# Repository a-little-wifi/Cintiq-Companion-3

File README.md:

# Cintiq Companion 3

I have a dead Cintiq 13HD (pen+touch) that won't display anything. I know the lcd works, tested it in my Cintiq Companion, so the board must be dead. I wanna make a new one, that you can build a computer into, or with USB-C maybe. 

Wacom made a tablet PC based on the 13HD called the Cintiq Companion, then they made a Cintiq Companion 2, so this will be the Cintiq Companion 3.

Contains a USB2514Bi 4-port USB hub connected as follows:

- Port 1: Pen digitizer?
- Port 2: External USB port
- Port 3: USB UART converter
- Port 4: Touch panel digitizer

I thought the USB UART chip (SILABS CP2102) was for the pen digitizer, but it appears to connect to the RTD2483AD display controller chip instead, might be for brightness control.

This is probably the right connector for the touch panel: https://www.lcsc.com/product-detail/Wire-To-Board-Connector_HCTL-HC-0-8-5PWT_C2845346.html  

Possible ipex connectors:  
https://www.lcsc.com/product-detail/Card-Edge-Connectors_JUSHUO-ALC04-S30EIA-00_C2842535.html  
https://www.lcsc.com/product-detail/FFC-FPC-Connectors_Lian-Xin-Technology-20455-030E-12_C7527730.html

The scanned images are 300ppi, for size reference

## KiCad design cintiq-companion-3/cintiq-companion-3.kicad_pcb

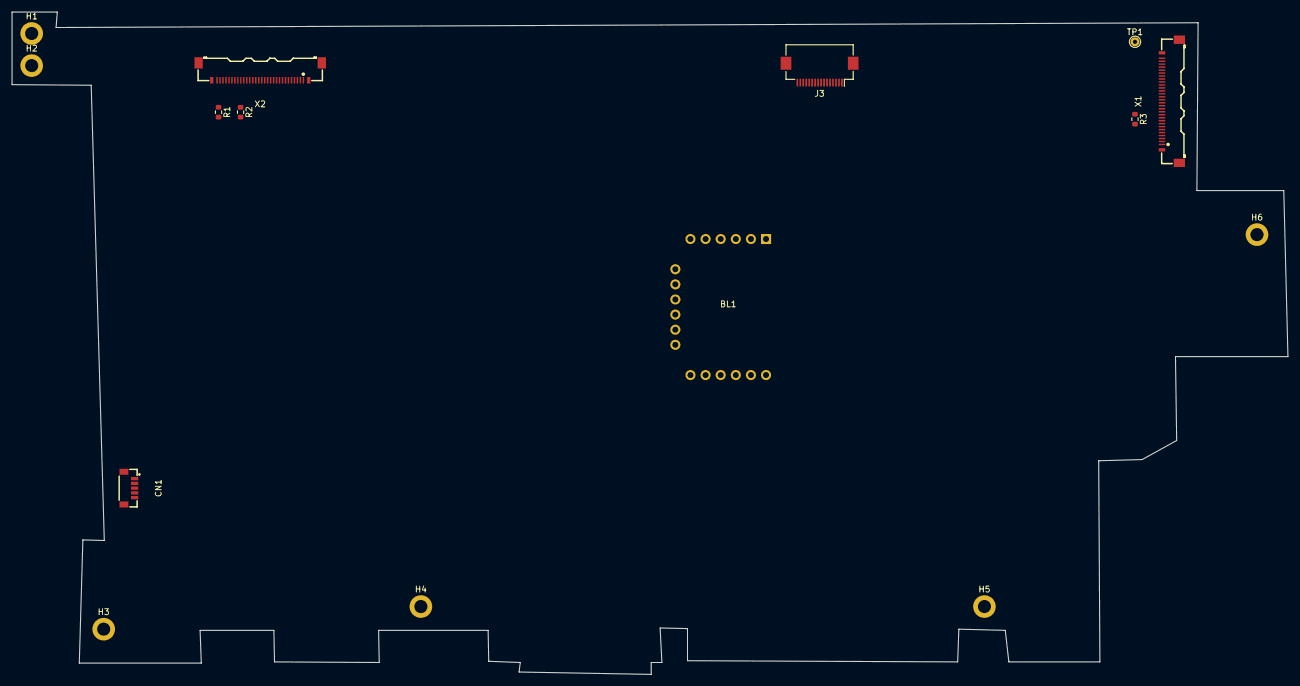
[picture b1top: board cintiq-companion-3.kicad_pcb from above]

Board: 2 copper layers, 214.4 x 111.3 mm, 15 parts (0 on the bottom side), 21 nets, no tracks yet.

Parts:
BL1: koyomi-backlight
CN1: 13HD_fingerpanel; minitek5p0.8mm
H1, H2, H3, H4, H5, H6: MountingHole_Pad; MountingHole_2.2mm_M2_DIN965_Pad
J3: 13HD_buttonboard; Hirose_FH12-16S-0.5SH_1x16-1MP_P0.50mm_Horizontal
R1, R2: 4.7kΩ; R_0603_1608Metric
R3: 47kΩ; R_0603_1608Metric
TP1: Something; TestPoint_THTPad_D1.5mm_Drill0.7mm
X1: 13HD_eDP; 30pipex
X2: 13HD_penpanel; 30pipex

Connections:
+3.3V: BL1.8 (+3.3V), J3.1, J3.2, X1.18, X1.19
+5V: BL1.4 (+5V), CN1.5, X2.10, X2.11
+VBL: BL1.1 (VAD), X1.4, X1.5
/BL_return_1: BL1.13 (LED1), X1.10
/BL_return_2: BL1.14 (LED2), X1.9
/BL_return_3: BL1.15 (LED3), X1.8
/BL_return_4: BL1.16 (LED4), X1.7
/RTD2483AD_pin_105: R1.1, X2.28
/RTD2483AD_pin_110: R2.1, X2.24
/bottombutton: J3.6, X2.19
/downbutton: J3.7, X2.15
/eDP_HPD: R3.1, X1.15
/leftbutton: J3.9, X2.16
/middlebottombutton: J3.5, X2.20
/middlebutton: J3.11, X2.14
/middletopbutton: J3.4, X2.21
/rightbutton: J3.10, X2.18
/topbutton: J3.3, X2.22
/upbutton: J3.8, X2.17
GND: BL1.3 (GND), BL1.7 (GND), CN1.1, CN1.6, CN1.7, H1.1, H2.1, H3.1, H4.1, H5.1, H6.1, J3.15, J3.16, J3.MP (MountPin), R1.2, R2.2, R3.2, X1.16, X1.20, X1.23, X1.26, X1.29, X1.31, X1.32, X1.33, X1.34, X2.5, X2.6, X2.12, X2.13, X2.23, X2.27, X2.31, X2.32, X2.33, X2.34
unnamed: TP1.1, X1.30

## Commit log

2024-05-09 Created KiCad project
2024-05-09 Added readme
2024-05-09 added generic connector symbols and connected ground pins
2024-05-09 Added marco pictures of connectors
2024-05-09 rotated images + ran some signals
2024-05-09 Added CP2102 usb uart bridge
2024-05-09 Added USB/UART notes to readme
2024-05-09 updated usb hub part number
2024-05-09 Added USB pins for touch and pen panels
2024-05-09 did a think
2024-05-09 Added picture of traces between button board and penpanel
2024-05-09 Added power rails
2024-05-09 Wired up all buttons
2024-05-09 Completed pinout + added full board pics
2024-05-09 Added eDP pinout/polarity
2024-05-09 Added image for checking the DP lane number and polarity based on the STDP4028 pinout
2024-05-10 Changed 30-pin symbols to ipex
2024-05-10 Created PCB file with some footprints
2024-05-10 Added touch panel USB footprint
2024-05-10 Approximate connector placement done
    Big board :skull:
2024-05-10 Added scans of the original board for checking dimensions
2024-05-10 Added note about scan scale
2024-05-10 Moved images to their own folder and added gimp file with measurements
2024-05-10 Added backlight controller footprint
2024-05-10 Finished gimp measurements
2024-05-11 Placed mount holes with image measurements but they aren't quite right
2024-05-11 schematic and pcb notes lol
2024-05-11 Horrible board outline
2024-05-31 Added LattePanda Mu to schematic
    this gonna be cool
2024-06-04 Added HSIO diagram to schematic
2024-06-04 Added more Intel diagrams
2024-06-04 Start schematic restructure
2024-06-04 Schematic in an ok state
2024-06-05 Fix CLKREQ numbering
2024-06-05 Made a little HSIO plan
2024-06-13 Did some footprint assignments and added reference image to pcb editor
2024-06-13 Redid board outline according to reference and placed compute module slot
2024-06-13 Added m.2 ssd slot, did some test routing
2024-06-13 Added E-key slot
2024-06-13 Added ground fill
2024-08-18 thicker backlight traces lol
2024-08-18 Disconnected so far unused things on schematic
2024-08-18 Clearer notes
2024-08-18 susclk
2024-08-19 renamed pcie nets
2024-08-19 routed usb
2024-08-19 Added B-key slot and dual bios chips
2024-08-19 Added USB3 and 2nd E-key link
2024-08-19 Started adding type-c
2024-09-02 flipped b-key lane order and added usb-c ports
2024-09-02 fancy netclass colors
2024-09-02 updated hsio description
2024-09-26 added todo note for eDP HPD
    might need to be inverted?
2024-10-22 ursus
2024-10-25 added sata gpios to symbol
2024-10-25 updated notes
2024-11-27 Swapped sata pair polarity on m-key slot to make sata actually work probably
2025-03-06 added links for ipex connectors to readme
2025-07-24 unflipped m-key polarity for sata
